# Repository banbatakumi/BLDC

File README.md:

# BLDC

自律走行ミニカー用の BLDC モータドライバ (MD)。**現行のファームは [ProgramV4](ProgramV4/)** (STM32F303K8、FOC、基板 CurcuitV4)。
ProgramV1〜V3 は旧版。

ProgramV4 の文書 (パラメータの意味と根拠の正は `ProgramV4/src/app/config.h`):

| 文書 | 内容 |
|---|---|
| [docs/FOC.md](ProgramV4/docs/FOC.md) | 制御の構成・エンコーダの扱い・スイッチ校正・ゲイン・保護 |
| [docs/SERIAL_PROTOCOL.md](ProgramV4/docs/SERIAL_PROTOCOL.md) | 上位 (STM32F446RE) との UART 通信仕様 |
| [docs/HARDWARE_MAP.md](ProgramV4/docs/HARDWARE_MAP.md) | 基板のピン・相・電流センスの対応 |
| [docs/OPTIMIZATION.md](ProgramV4/docs/OPTIMIZATION.md) | 性能の設計理由・実行時間・残課題 |

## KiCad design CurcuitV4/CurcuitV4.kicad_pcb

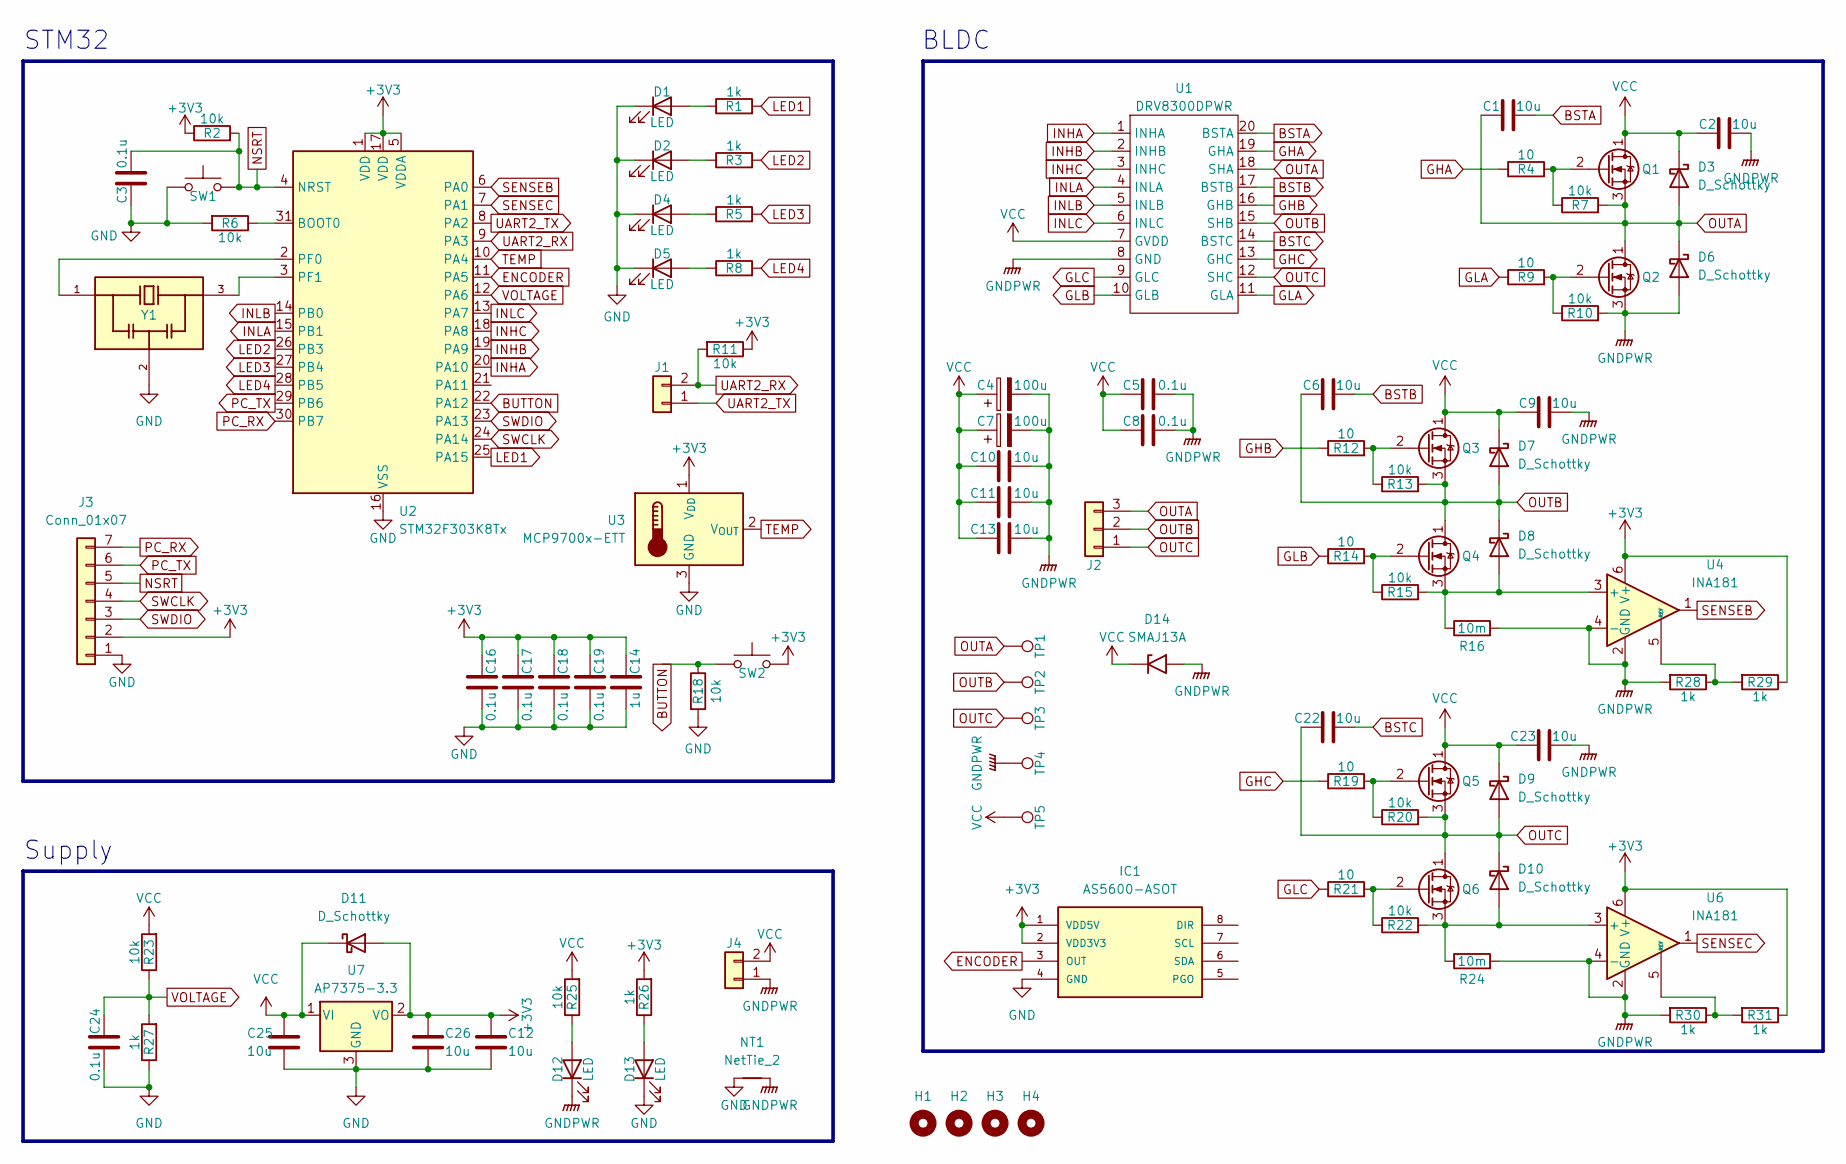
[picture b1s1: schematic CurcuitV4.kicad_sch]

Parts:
C1, C2, C6, C9, C10, C11, C12, C13, C22, C23, C25, C26: 10u; C_0805_2012Metric
C3, C5, C8, C16, C17, C18, C19, C24: 0.1u; C_0603_1608Metric
C4, C7: 100u; CP_Radial_D6.3mm_P2.50mm
C14: 1u; C_0603_1608Metric
D1, D2, D4, D5, D12, D13: LED; LED_0603_1608Metric
D3, D6, D7, D8, D9, D10, D11: D_Schottky; D_SOD-323_HandSoldering
D14: SMAJ13A; D_SMA
H1, H2, H3, H4: MountingHole; MountingHole_3.2mm_M3_ISO14580_Pad_TopBottom
IC1: AS5600-ASOT; SOIC-8_3.9x4.9mm_P1.27mm; MOUSER_PART_NUMBER 985-AS5600-ASOT
J1: Conn_01x02; JST_PH_S2B-PH-K_1x02_P2.00mm_Horizontal
J2: Conn_01x03; Molex_SPOX_5268-03A_1x03_P2.50mm_Horizontal
J3: Conn_01x07; PinSocket_1x07_P2.54mm_Vertical
J4: Conn_01x02; Molex_SPOX_5268-02A_1x02_P2.50mm_Horizontal
NT1: NetTie_2; NetTie-2_SMD_Pad0.5mm
Q1, Q2, Q3, Q4, Q5, Q6: Q_NMOS_DGS; SSM6K819R
R1, R3, R5, R8, R26, R27, R28, R29, R30, R31: 1k; R_0603_1608Metric
R2, R6, R7, R10, R11, R13, R15, R18, R20, R22, R23, R25: 10k; R_0603_1608Metric
R4, R9, R12, R14, R19, R21: 10; R_0603_1608Metric
R16, R24: 10m; R_1206_3216Metric
SW1, SW2: SW_Push; SW_Push_1P1T_NO_Vertical_Wuerth_434133025816
TP1, TP2, TP3, TP4, TP5: TestPoint; TestPoint_Pad_D2.5mm
U1: DRV8300DPWR; TSSOP-20_4.4x6.5mm_P0.65mm
U2: STM32F303K8Tx; LQFP-32_7x7mm_P0.8mm
U3: MCP9700x-ETT; SOT-23
U4, U6: INA181; SOT-23-6
U7: AP7375-3.3; SOT-23
Y1: CSTNE16M0V530000R0; Resonator_SMD_Murata_CSTxExxV-3Pin_3.0x1.1mm; PARTREV JGC42-8853B

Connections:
+3V3: C12.1, C14.2, C16.2, C17.2, C18.2, C19.2, C26.1, D11.2 (A), IC1.1 (VDD5V), IC1.2 (VDD3V3), J3.2, R2.1, R11.1, R26.2, R29.1, R31.1, SW2.2, U2.1 (VDD), U2.5 (VDDA), U2.17 (VDD), U3.1 (V_{DD}), U4.6 (V+), U6.6 (V+), U7.2 (VO)
BSTA: C1.2, U1.20 (BSTA)
BSTB: C6.2, U1.17 (BSTB)
BSTC: C22.2, U1.14 (BSTC)
BUTTON: R18.1, SW2.1, U2.22 (PA12)
ENCODER: IC1.3 (OUT), U2.11 (PA5)
GHA: R4.1, U1.19 (GHA)
GHB: R12.1, U1.16 (GHB)
GHC: R19.1, U1.13 (GHC)
GLA: R9.1, U1.11 (GLA)
GLB: R14.1, U1.10 (GLB)
GLC: R21.1, U1.9 (GLC)
GND: C3.2, C12.2, C14.1, C16.1, C17.1, C18.1, C19.1, C24.1, C25.2, C26.2, D1.1 (K), D2.1 (K), D4.1 (K), D5.1 (K), D13.1 (K), IC1.4 (GND), J3.1, NT1.1, R6.2, R18.2, R27.1, SW1.1, U2.16 (VSS), U2.32 (VSS), U3.3 (GND), U7.3 (GND), Y1.2
GNDPWR: C2.2, C4.2, C5.1, C7.2, C8.1, C9.2, C10.1, C11.1, C13.1, C23.2, D6.2 (A), D12.1 (K), D14.2 (A2), J4.1, NT1.2, Q2.3 (S), R10.2, R16.2, R24.2, R28.2, R30.2, TP4.1, U1.8 (GND), U4.2 (GND), U4.4 (-), U6.2 (GND), U6.4 (-)
INHA: U1.1 (INHA), U2.20 (PA10)
INHB: U1.2 (INHB), U2.19 (PA9)
INHC: U1.3 (INHC), U2.18 (PA8)
INLA: U1.4 (INLA), U2.15 (PB1)
INLB: U1.5 (INLB), U2.14 (PB0)
INLC: U1.6 (INLC), U2.13 (PA7)
LED1: R1.2, U2.25 (PA15)
LED2: R3.2, U2.26 (PB3)
LED3: R5.2, U2.27 (PB4)
LED4: R8.2, U2.28 (PB5)
NSRT: C3.1, J3.5, R2.2, SW1.2, U2.4 (NRST)
unnamed: D1.2 (A), R1.1
unnamed: D2.2 (A), R3.1
unnamed: D4.2 (A), R5.1
unnamed: D5.2 (A), R8.1
unnamed: D8.2 (A), Q4.3 (S), R15.2, R16.1, U4.3 (+)
unnamed: D10.2 (A), Q6.3 (S), R22.2, R24.1, U6.3 (+)
unnamed: D12.2 (A), R25.1
unnamed: D13.2 (A), R26.1
unnamed: Q1.2 (G), R4.2, R7.1
unnamed: Q2.2 (G), R9.2, R10.1
unnamed: Q3.2 (G), R12.2, R13.1
unnamed: Q4.2 (G), R14.2, R15.1
unnamed: Q5.2 (G), R19.2, R20.1
unnamed: Q6.2 (G), R21.2, R22.1
unnamed: R6.1, U2.31 (BOOT0)
unnamed: U2.2 (PF0), Y1.1
unnamed: U2.3 (PF1), Y1.3
unnamed: R28.1, R29.2, U4.5 (REF)
unnamed: R30.1, R31.2, U6.5 (REF)
OUTA: C1.1, D3.2 (A), D6.1 (K), J2.3, Q1.3 (S), Q2.1 (D), R7.2, TP1.1, U1.18 (SHA)
OUTB: C6.1, D7.2 (A), D8.1 (K), J2.2, Q3.3 (S), Q4.1 (D), R13.2, TP2.1, U1.15 (SHB)
OUTC: C22.1, D9.2 (A), D10.1 (K), J2.1, Q5.3 (S), Q6.1 (D), R20.2, TP3.1, U1.12 (SHC)
PC_RX: J3.7, U2.30 (PB7)
PC_TX: J3.6, U2.29 (PB6)
SENSEB: U2.6 (PA0), U4.1
SENSEC: U2.7 (PA1), U6.1
SWCLK: J3.4, U2.24 (PA14)
SWDIO: J3.3, U2.23 (PA13)
TEMP: U2.10 (PA4), U3.2 (V_{OUT})
UART2_RX: J1.2, R11.2, U2.9 (PA3)
UART2_TX: J1.1, U2.8 (PA2)
VCC: C2.1, C4.1, C5.2, C7.1, C8.2, C9.1, C10.2, C11.2, C13.2, C23.1, C25.1, D3.1 (K), D7.1 (K), D9.1 (K), D11.1 (K), D14.1 (A1), J4.2, Q1.1 (D), Q3.1 (D), Q5.1 (D), R23.2, R25.2, TP5.1, U1.7 (GVDD), U7.1 (VI)
VOLTAGE: C24.2, R23.1, R27.2, U2.12 (PA6)

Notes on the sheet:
Supply
STM32
BLDC

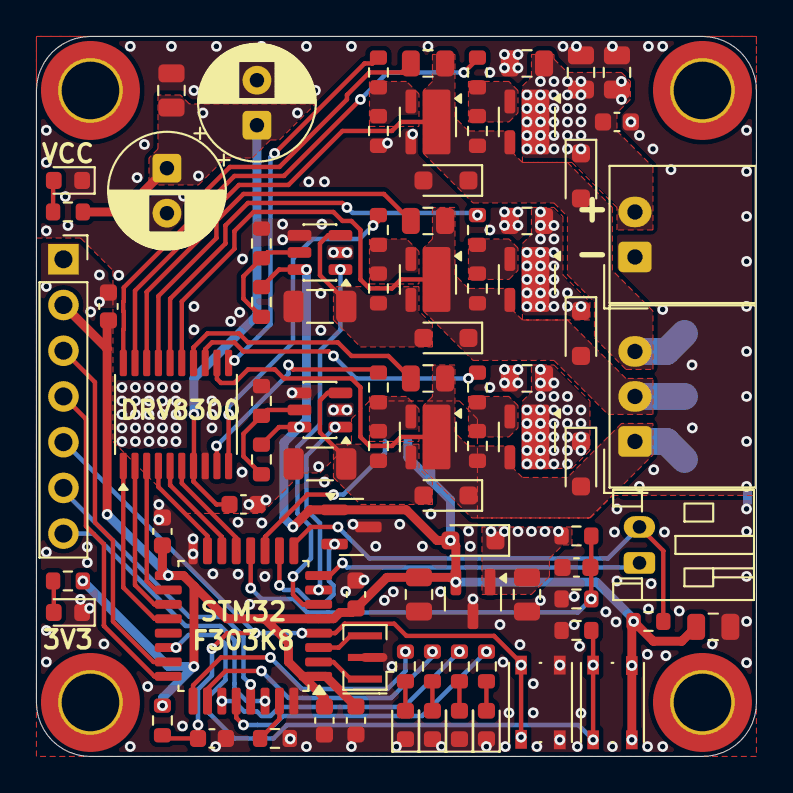
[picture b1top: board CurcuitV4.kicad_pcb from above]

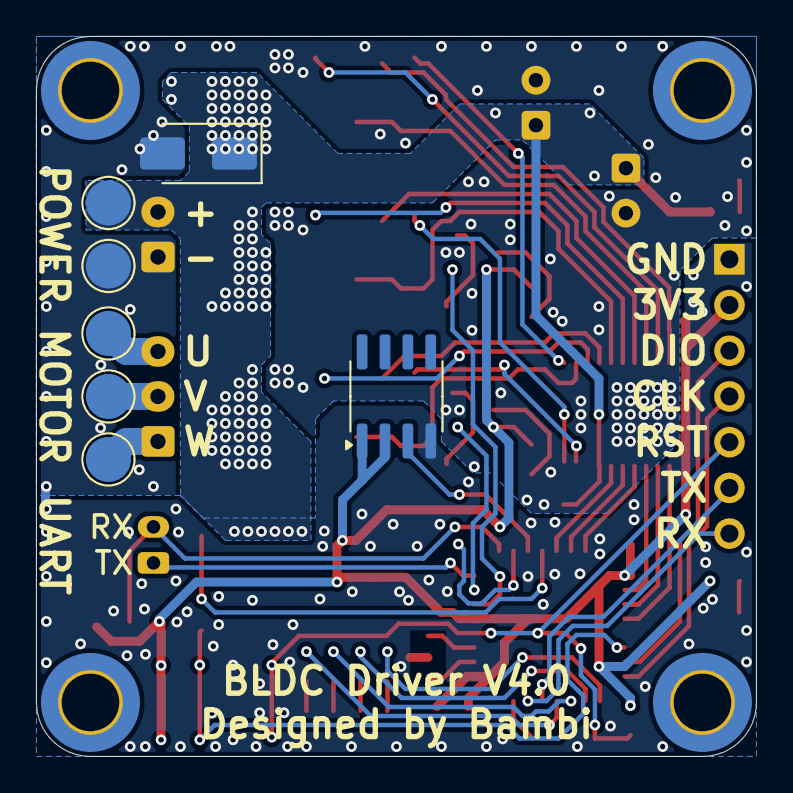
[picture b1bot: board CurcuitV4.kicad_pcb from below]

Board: 2 copper layers, 40.0 x 40.0 mm, 97 parts (8 on the bottom side), 58 nets.

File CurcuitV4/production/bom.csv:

Designator,Footprint,Quantity,Value,LCSC Part #
"C1, C10, C11, C12, C13, C2, C22, C23, C25, C26, C6, C9",0805,12,10u,
C14,0603,1,1u,
"C16, C17, C18, C19, C24, C3, C5, C8",0603,8,0.1u,
"C4, C7",CP_Radial_D6.3mm_P2.50mm,2,100u,
"D1, D12, D13, D2, D4, D5",0603,6,LED,
"D10, D11, D3, D6, D7, D8, D9",D_SOD-323_HandSoldering,7,D_Schottky,
D14,D_SMA,1,SMAJ13A,
IC1,SOIC-8_3.9x4.9mm_P1.27mm,1,AS5600-ASOT,
J1,JST_PH_S2B-PH-K_1x02_P2.00mm_Horizontal,1,Conn_01x02,
J2,Molex_SPOX_5268-03A_1x03_P2.50mm_Horizontal,1,Conn_01x03,
J3,PinSocket_1x07_P2.54mm_Vertical,1,Conn_01x07,
J4,Molex_SPOX_5268-02A_1x02_P2.50mm_Horizontal,1,Conn_01x02,
"Q1, Q2, Q3, Q4, Q5, Q6",SSM6K819R,6,Q_NMOS_DGS,
"R1, R26, R27, R28, R29, R3, R30, R31, R5, R8",0603,10,1k,
"R10, R11, R13, R15, R18, R2, R20, R22, R23, R25, R6, R7",0603,12,10k,
"R12, R14, R19, R21, R4, R9",0603,6,10,
"R16, R24",1206,2,10m,
"SW1, SW2",SW_Push_1P1T_NO_Vertical_Wuerth_434133025816,2,SW_Push,
"TP1, TP2, TP3, TP4, TP5",TestPoint_Pad_D2.5mm,5,TestPoint,
U1,TSSOP-20_4.4x6.5mm_P0.65mm,1,DRV8300DPWR,
U2,LQFP-32_7x7mm_P0.8mm,1,STM32F303K8Tx,
U3,SOT-23,1,MCP9700x-ETT,
"U4, U6",SOT-23-6,2,INA181,
U7,SOT-23,1,AP7375-3.3,
Y1,Resonator_SMD_Murata_CSTxExxV-3Pin_3.0x1.1mm,1,CSTNE16M0V530000R0,

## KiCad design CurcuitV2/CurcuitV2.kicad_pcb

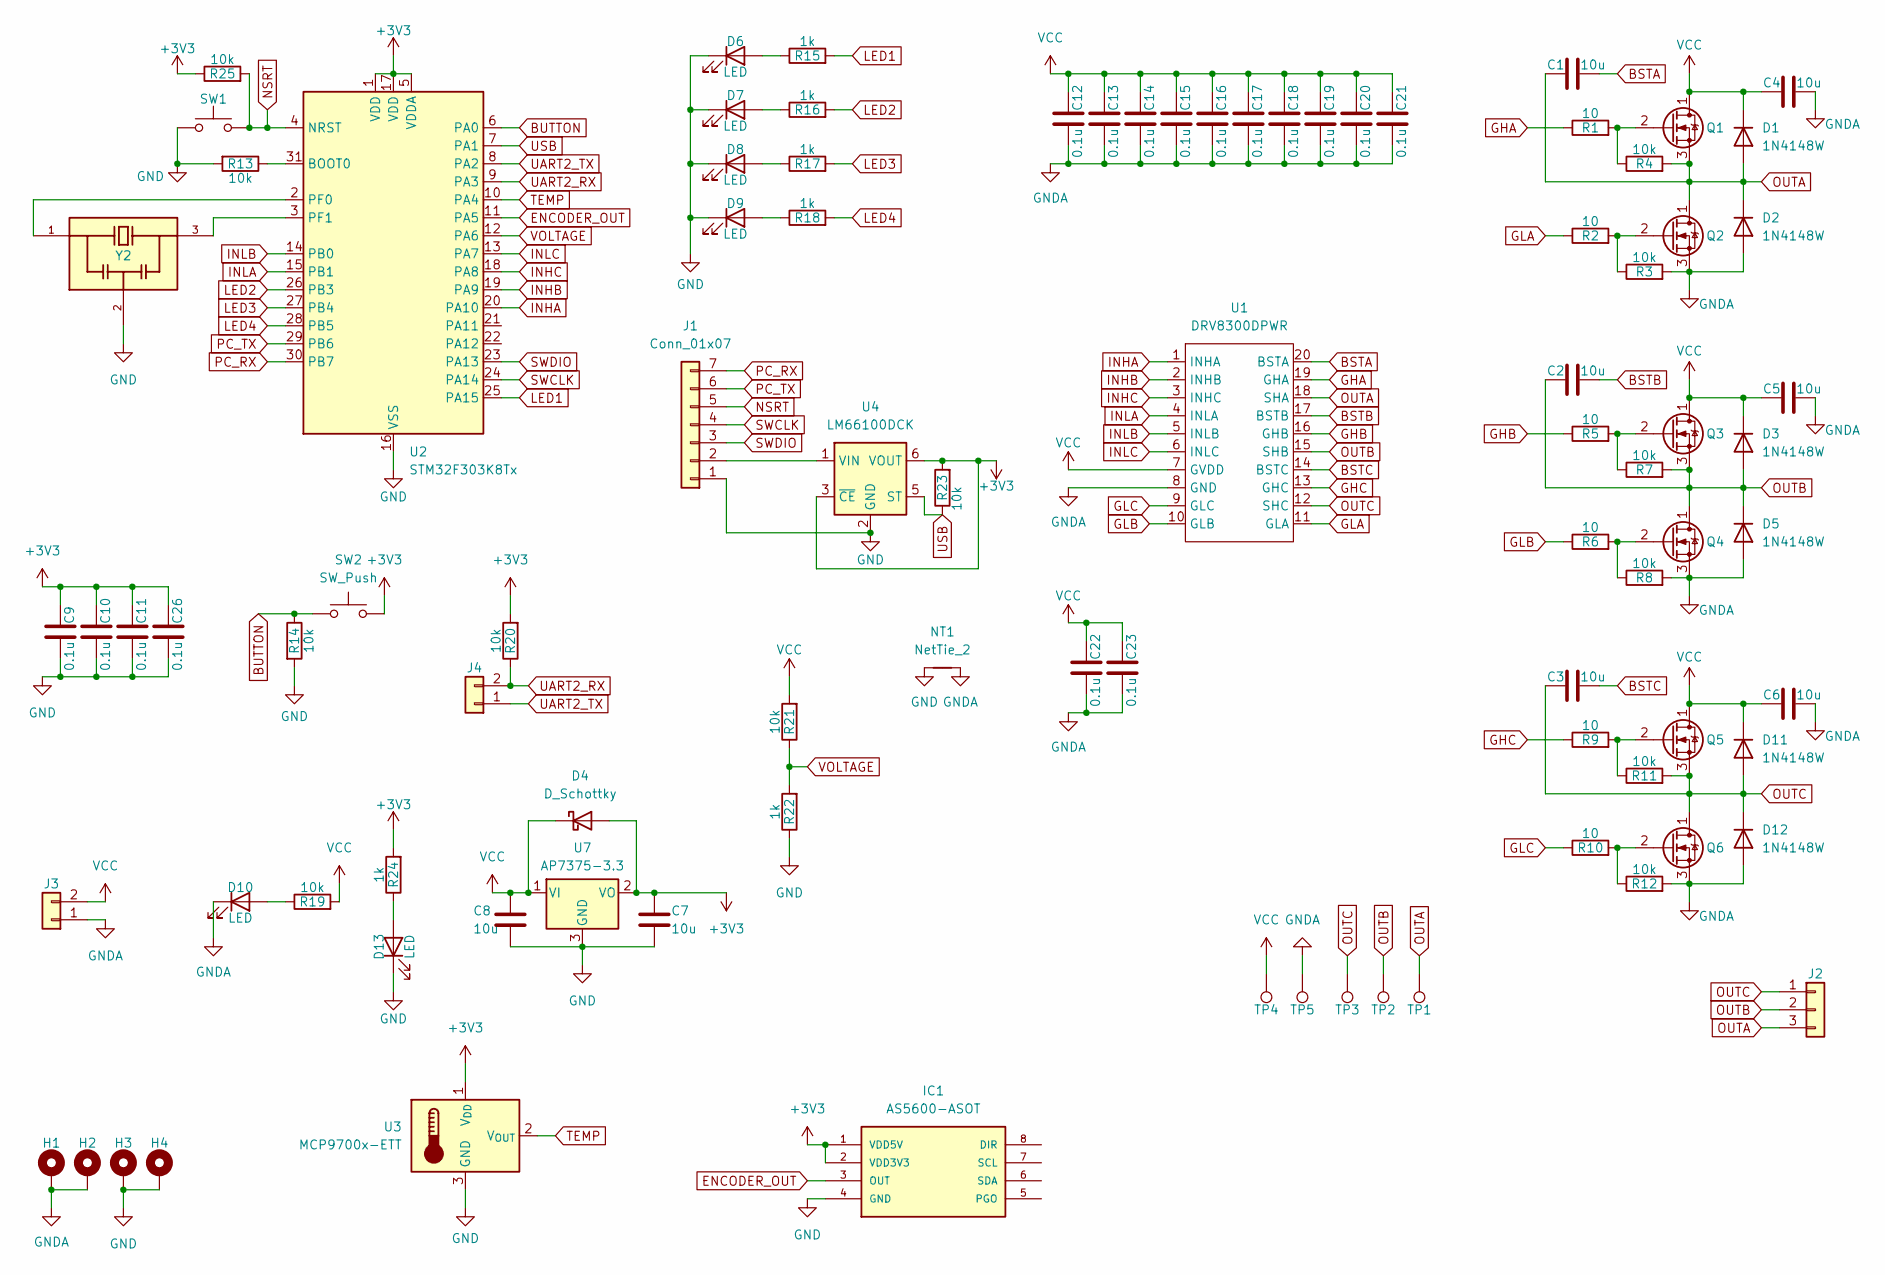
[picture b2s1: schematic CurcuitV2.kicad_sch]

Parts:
C1, C2, C3, C4, C5, C6, C7, C8: 10u; C_0805_2012Metric
C9, C10, C11, C22, C26: 0.1u; C_0603_1608Metric
C12, C13, C14, C15, C16, C17, C18, C19, C20, C21, C23: 0.1u; C_0805_2012Metric
D1, D2, D3, D5, D11, D12: 1N4148W; D_SOD-123
D4: D_Schottky; D_SOD-323_HandSoldering
D6, D7, D8, D9, D10, D13: LED; LED_0603_1608Metric
H1, H2, H3, H4: MountingHole_Pad; MountingHole_3.2mm_M3_ISO14580_Pad_TopBottom
IC1: AS5600-ASOT; SOIC-8_3.9x4.9mm_P1.27mm; MOUSER_PART_NUMBER 985-AS5600-ASOT
J1: Conn_01x07; PinSocket_1x07_P2.54mm_Vertical
J2: Conn_01x03; JST_XH_S3B-XH-A_1x03_P2.50mm_Horizontal
J3: Conn_01x02; JST_XH_S2B-XH-A_1x02_P2.50mm_Horizontal
J4: Conn_01x02; JST_PH_S2B-PH-K_1x02_P2.00mm_Horizontal
NT1: NetTie_2; NetTie-2_SMD_Pad2.0mm
Q1, Q2, Q3, Q4, Q5, Q6: Q_NMOS_DGS; SSM6K819R
R1, R2, R5, R6, R9, R10: 10; R_0603_1608Metric
R3, R4, R7, R8, R11, R12, R13, R14, R19, R20, R21, R23, R25: 10k; R_0603_1608Metric
R15, R16, R17, R18, R22, R24: 1k; R_0603_1608Metric
SW1, SW2: SW_Push; SW_Push_1P1T_NO_Vertical_Wuerth_434133025816
TP1, TP2, TP3, TP4, TP5: TestPoint; TestPoint_Pad_D2.5mm
U1: DRV8300DPWR; TSSOP-20_4.4x6.5mm_P0.65mm
U2: STM32F303K8Tx; LQFP-32_7x7mm_P0.8mm
U3: MCP9700x-ETT; SOT-23
U4: LM66100DCK; SOT-363_SC-70-6
U7: AP7375-3.3; SOT-23
Y2: CSTNE16M0V530000R0; Resonator_SMD_Murata_CSTxExxV-3Pin_3.0x1.1mm; PARTREV JGC42-8853B

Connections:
+3V3: C7.1, C9.2, C10.2, C11.2, C26.2, D4.2 (A), IC1.1 (VDD5V), IC1.2 (VDD3V3), R20.2, R23.2, R24.2, R25.1, SW2.2, U2.1 (VDD), U2.5 (VDDA), U2.17 (VDD), U3.1 (V_{DD}), U4.3 (~CE), U4.6 (VOUT), U7.2 (VO)
BSTA: C1.2, U1.20 (BSTA)
BSTB: C2.2, U1.17 (BSTB)
BSTC: C3.2, U1.14 (BSTC)
BUTTON: R14.1, SW2.1, U2.6 (PA0)
ENCODER_OUT: IC1.3 (OUT), U2.11 (PA5)
GHA: R1.1, U1.19 (GHA)
GHB: R5.1, U1.16 (GHB)
GHC: R9.1, U1.13 (GHC)
GLA: R2.1, U1.11 (GLA)
GLB: R6.1, U1.10 (GLB)
GLC: R10.1, U1.9 (GLC)
GND: C7.2, C8.2, C9.1, C10.1, C11.1, C26.1, D6.1 (K), D7.1 (K), D8.1 (K), D9.1 (K), D13.1 (K), H3.1, H4.1, IC1.4 (GND), J1.1, NT1.1, R13.2, R14.2, R22.1, SW1.1, U2.16 (VSS), U2.32 (VSS), U3.3 (GND), U4.2 (GND), U7.3 (GND), Y2.2; also elsewhere on the board
GNDA: C4.2, C5.2, C6.2, C12.1, C13.1, C14.1, C15.1, C16.1, C17.1, C18.1, C19.1, C20.1, C21.1, C22.1, C23.1, D2.2 (A), D5.2 (A), D10.1 (K), D12.2 (A), H1.1, H2.1, J3.1, NT1.2, Q2.3 (S), Q4.3 (S), Q6.3 (S), R3.2, R8.2, R12.2, TP5.1, U1.8 (GND)
INHA: U1.1 (INHA), U2.20 (PA10)
INHB: U1.2 (INHB), U2.19 (PA9)
INHC: U1.3 (INHC), U2.18 (PA8)
INLA: U1.4 (INLA), U2.15 (PB1)
INLB: U1.5 (INLB), U2.14 (PB0)
INLC: U1.6 (INLC), U2.13 (PA7)
LED1: R15.2, U2.25 (PA15)
LED2: R16.2, U2.26 (PB3)
LED3: R17.2, U2.27 (PB4)
LED4: R18.2, U2.28 (PB5)
NSRT: J1.5, R25.2, SW1.2, U2.4 (NRST); also elsewhere on the board
unnamed: D6.2 (A), R15.1
unnamed: D7.2 (A), R16.1
unnamed: D8.2 (A), R17.1
unnamed: D9.2 (A), R18.1
unnamed: D10.2 (A), R19.1
unnamed: D13.2 (A), R24.1
unnamed: J1.2, U4.1 (VIN)
unnamed: Q1.2 (G), R1.2, R4.1
unnamed: Q2.2 (G), R2.2, R3.1
unnamed: Q3.2 (G), R5.2, R7.1
unnamed: Q4.2 (G), R6.2, R8.1
unnamed: Q5.2 (G), R9.2, R11.1
unnamed: Q6.2 (G), R10.2, R12.1
unnamed: R13.1, U2.31 (BOOT0)
unnamed: U2.2 (PF0), Y2.1
unnamed: U2.3 (PF1), Y2.3
OUTA: C1.1, D1.2 (A), D2.1 (K), J2.3, Q1.3 (S), Q2.1 (D), R4.2, TP1.1, U1.18 (SHA)
OUTB: C2.1, D3.2 (A), D5.1 (K), J2.2, Q3.3 (S), Q4.1 (D), R7.2, TP2.1, U1.15 (SHB)
OUTC: C3.1, D11.2 (A), D12.1 (K), J2.1, Q5.3 (S), Q6.1 (D), R11.2, TP3.1, U1.12 (SHC)
PC_RX: J1.7, U2.30 (PB7)
PC_TX: J1.6, U2.29 (PB6)
SWCLK: J1.4, U2.24 (PA14)
SWDIO: J1.3, U2.23 (PA13)
TEMP: U2.10 (PA4), U3.2 (V_{OUT})
UART2_RX: J4.2, R20.1, U2.9 (PA3)
UART2_TX: J4.1, U2.8 (PA2)
USB: R23.1, U2.7 (PA1), U4.5 (ST)
VCC: C4.1, C5.1, C6.1, C8.1, C12.2, C13.2, C14.2, C15.2, C16.2, C17.2, C18.2, C19.2, C20.2, C21.2, C22.2, C23.2, D1.1 (K), D3.1 (K), D4.1 (K), D11.1 (K), J3.2, Q1.1 (D), Q3.1 (D), Q5.1 (D), R19.2, R21.2, TP4.1, U1.7 (GVDD), U7.1 (VI)
VOLTAGE: R21.1, R22.2, U2.12 (PA6)

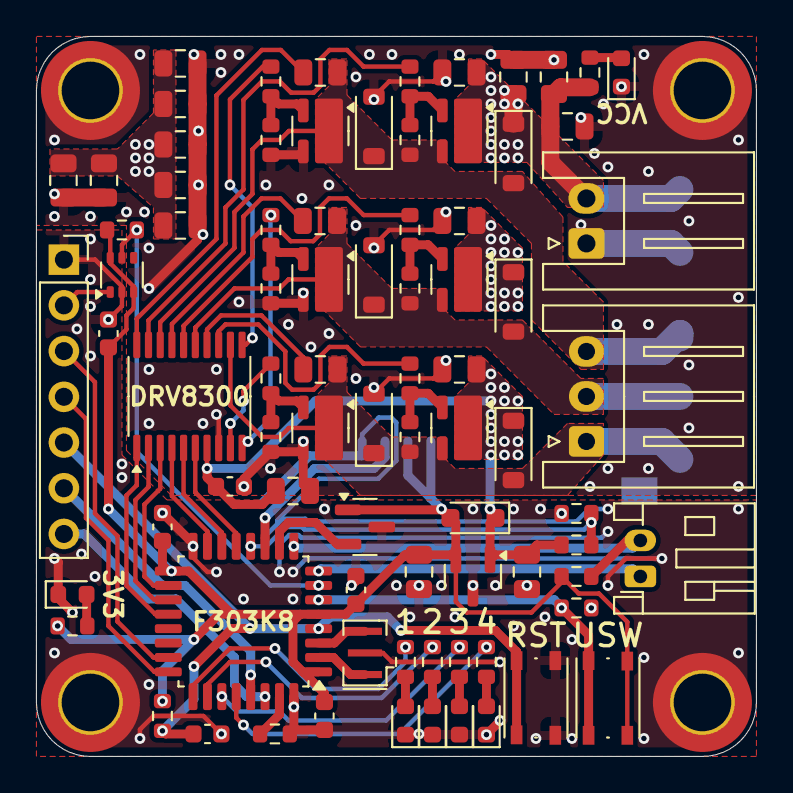
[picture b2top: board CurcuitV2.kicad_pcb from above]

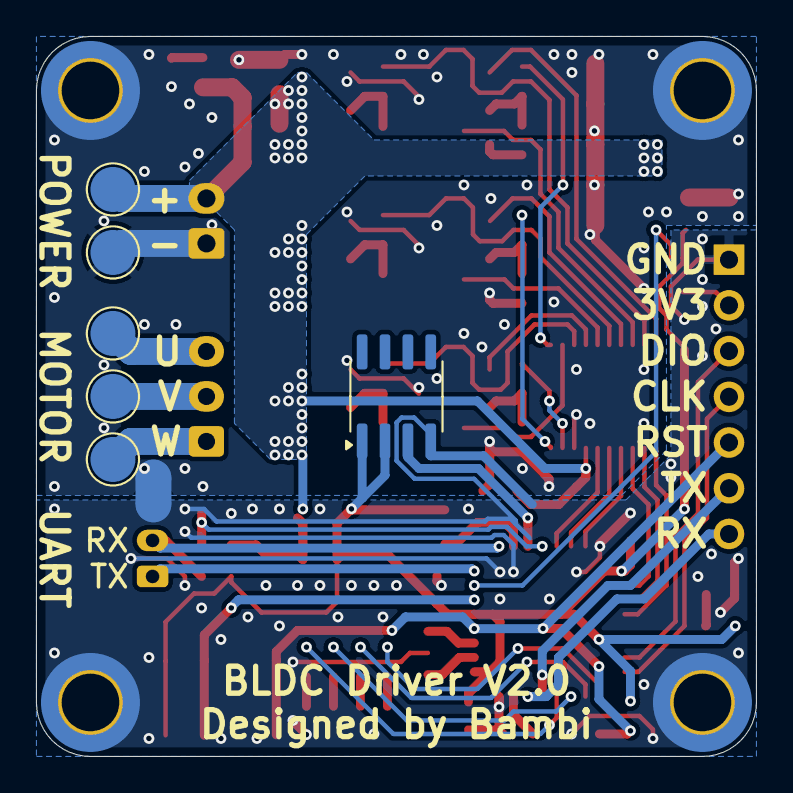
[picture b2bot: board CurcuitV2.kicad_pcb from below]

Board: 2 copper layers, 40.0 x 40.0 mm, 92 parts (7 on the bottom side), 54 nets.

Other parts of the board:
C24: 0.1u; C_0603_1608Metric

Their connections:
GND: C24.2; also elsewhere on the board
NSRT: C24.1; also elsewhere on the board

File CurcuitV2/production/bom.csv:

Designator,Footprint,Quantity,Value,LCSC Part #
"C1, C2, C3, C4, C5, C6, C7, C8",0805,8,10u,
"C10, C11, C22, C26, C9",0603,5,0.1u,
"C12, C13, C14, C15, C16, C17, C18, C19, C20, C21, C23",0805,11,0.1u,
"D1, D11, D12, D2, D3, D5",D_SOD-123,6,1N4148W,
"D10, D13, D6, D7, D8, D9",0603,6,LED,
D4,D_SOD-323_HandSoldering,1,D_Schottky,
IC1,SOIC-8_3.9x4.9mm_P1.27mm,1,AS5600-ASOT,
J1,PinSocket_1x07_P2.54mm_Vertical,1,Conn_01x07,
J2,JST_XH_S3B-XH-A_1x03_P2.50mm_Horizontal,1,Conn_01x03,
J3,JST_XH_S2B-XH-A_1x02_P2.50mm_Horizontal,1,Conn_01x02,
J4,JST_PH_S2B-PH-K_1x02_P2.00mm_Horizontal,1,Conn_01x02,
"Q1, Q2, Q3, Q4, Q5, Q6",SSM6K819R,6,Q_NMOS_DGS,
"R1, R10, R2, R5, R6, R9",0603,6,10,
"R11, R12, R13, R14, R19, R20, R21, R23, R3, R4, R7, R8",0603,12,10k,
"R15, R16, R17, R18, R22, R24",0603,6,1k,
"SW1, SW2",SW_Push_1P1T_NO_Vertical_Wuerth_434133025816,2,SW_Push,
"TP1, TP2, TP3, TP4, TP5",TestPoint_Pad_D2.5mm,5,TestPoint,
U1,TSSOP-20_4.4x6.5mm_P0.65mm,1,DRV8300DPWR,
U2,LQFP-32_7x7mm_P0.8mm,1,STM32F303K8Tx,
U3,SOT-23,1,MCP9700x-ETT,
U4,SOT-363_SC-70-6,1,LM66100DCK,
U7,SOT-23,1,AP7375-3.3,
Y2,Resonator_SMD_Murata_CSTxExxV-3Pin_3.0x1.1mm,1,CSTNE16M0V530000R0,

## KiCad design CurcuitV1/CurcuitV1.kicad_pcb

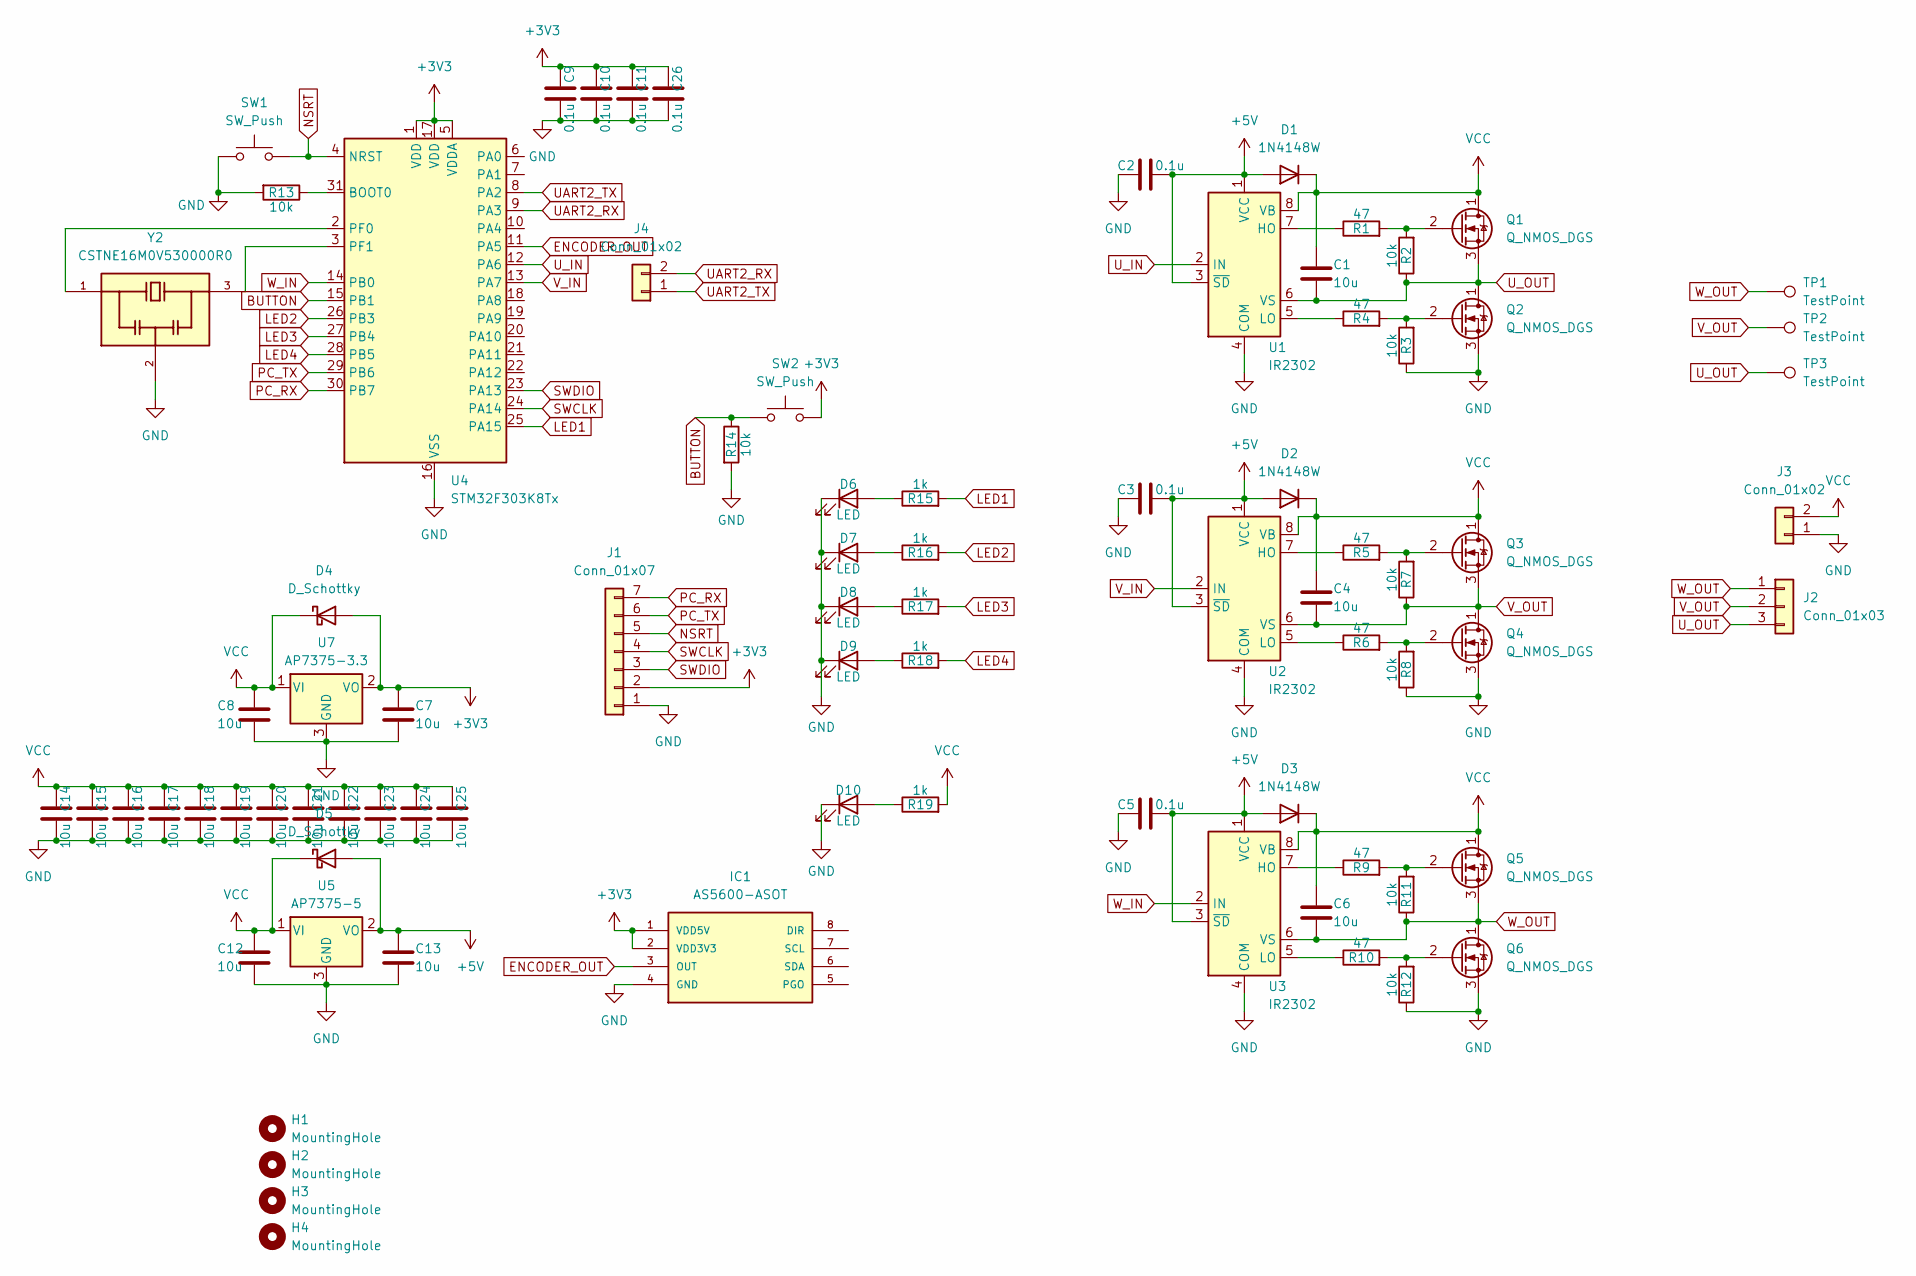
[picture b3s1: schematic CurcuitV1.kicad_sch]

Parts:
C1, C4, C6, C7, C8, C12, C13, C14, C15, C16, C17, C18, C19, C20, C21, C22, C23, C24, C25: 10u; C_0805_2012Metric
C2, C3, C5, C9, C10, C11, C26: 0.1u; C_0603_1608Metric
D1, D2, D3: 1N4148W; D_SOD-123
D4, D5: D_Schottky; D_SOD-323_HandSoldering
D6, D7, D8, D9, D10: LED; LED_0603_1608Metric
H1, H2, H3, H4: MountingHole; MountingHole_3.2mm_M3_DIN965_Pad
IC1: AS5600-ASOT; SOIC-8_3.9x4.9mm_P1.27mm; MOUSER_PART_NUMBER 985-AS5600-ASOT
J1: Conn_01x07; PinSocket_1x07_P2.54mm_Vertical
J2: Conn_01x03; JST_XH_S3B-XH-A_1x03_P2.50mm_Horizontal
J3, J4: Conn_01x02; JST_XH_S2B-XH-A_1x02_P2.50mm_Horizontal
Q1, Q2, Q3, Q4, Q5, Q6: Q_NMOS_DGS; SSM6K819R
R1, R4, R5, R6, R9, R10: 47; R_0603_1608Metric
R2, R3, R7, R8, R11, R12, R13, R14: 10k; R_0603_1608Metric
R15, R16, R17, R18, R19: 1k; R_0603_1608Metric
SW1, SW2: SW_Push; SW_Push_1P1T_NO_Vertical_Wuerth_434133025816
TP1, TP2, TP3: TestPoint; TestPoint_Pad_D2.0mm
U1, U2, U3: IR2302; SOP-8_3.9x4.9mm_P1.27mm
U4: STM32F303K8Tx; LQFP-32_7x7mm_P0.8mm
U5: AP7375-5; SOT-23
U7: AP7375-3.3; SOT-23
Y2: CSTNE16M0V530000R0; OSC_CSTNE16M0V530000R0; PARTREV JGC42-8853B

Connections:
+3V3: C7.1, C9.2, C10.2, C11.2, C26.2, D4.2 (A), IC1.1 (VDD5V), IC1.2 (VDD3V3), J1.2, SW2.2, U4.1 (VDD), U4.5 (VDDA), U4.17 (VDD), U7.2 (VO)
+5V: C2.1, C3.1, C5.1, C13.1, D1.2 (A), D2.2 (A), D3.2 (A), D5.2 (A), U1.1 (VCC), U1.3 (~SD), U2.1 (VCC), U2.3 (~SD), U3.1 (VCC), U3.3 (~SD), U5.2 (VO)
BUTTON: R14.1, SW2.1, U4.15 (PB1)
ENCODER_OUT: IC1.3 (OUT), U4.11 (PA5)
GND: C2.2, C3.2, C5.2, C7.2, C8.2, C9.1, C10.1, C11.1, C12.2, C13.2, C14.1, C15.1, C16.1, C17.1, C18.1, C19.1, C20.1, C21.1, C22.1, C23.1, C24.1, C25.1, C26.1, D6.1 (K), D7.1 (K), D8.1 (K), D9.1 (K), D10.1 (K), IC1.4 (GND), J1.1, J3.1, Q2.3 (S), Q4.3 (S), Q6.3 (S), R3.1, R8.1, R12.1, R13.2, R14.2, SW1.1, U1.4 (COM), U2.4 (COM), U3.4 (COM), U4.16 (VSS), U4.32 (VSS), U5.3 (GND), U7.3 (GND), Y2.2
LED1: R15.2, U4.25 (PA15)
LED2: R16.2, U4.26 (PB3)
LED3: R17.2, U4.27 (PB4)
LED4: R18.2, U4.28 (PB5)
NSRT: J1.5, SW1.2, U4.4 (NRST)
unnamed: D6.2 (A), R15.1
unnamed: D7.2 (A), R16.1
unnamed: D8.2 (A), R17.1
unnamed: D9.2 (A), R18.1
unnamed: D10.2 (A), R19.1
unnamed: Q1.2 (G), R1.2, R2.2
unnamed: Q2.2 (G), R3.2, R4.2
unnamed: Q3.2 (G), R5.2, R7.2
unnamed: Q4.2 (G), R6.2, R8.2
unnamed: Q5.2 (G), R9.2, R11.2
unnamed: Q6.2 (G), R10.2, R12.2
unnamed: R1.1, U1.7 (HO)
unnamed: R4.1, U1.5 (LO)
unnamed: R5.1, U2.7 (HO)
unnamed: R6.1, U2.5 (LO)
unnamed: R9.1, U3.7 (HO)
unnamed: R10.1, U3.5 (LO)
unnamed: R13.1, U4.31 (BOOT0)
unnamed: U4.2 (PF0), Y2.1
unnamed: U4.3 (PF1), Y2.3
PC_RX: J1.7, U4.30 (PB7)
PC_TX: J1.6, U4.29 (PB6)
SWCLK: J1.4, U4.24 (PA14)
SWDIO: J1.3, U4.23 (PA13)
UART2_RX: J4.2, U4.9 (PA3)
UART2_TX: J4.1, U4.8 (PA2)
U_IN: U1.2 (IN), U4.12 (PA6)
U_OUT: C1.2, J2.3, Q1.3 (S), Q2.1 (D), R2.1, TP3.1, U1.6 (VS)
VCC: C1.1, C4.1, C6.1, C8.1, C12.1, C14.2, C15.2, C16.2, C17.2, C18.2, C19.2, C20.2, C21.2, C22.2, C23.2, C24.2, C25.2, D1.1 (K), D2.1 (K), D3.1 (K), D4.1 (K), D5.1 (K), J3.2, Q1.1 (D), Q3.1 (D), Q5.1 (D), R19.2, U1.8 (VB), U2.8 (VB), U3.8 (VB), U5.1 (VI), U7.1 (VI)
V_IN: U2.2 (IN), U4.13 (PA7)
V_OUT: C4.2, J2.2, Q3.3 (S), Q4.1 (D), R7.1, TP2.1, U2.6 (VS)
W_IN: U3.2 (IN), U4.14 (PB0)
W_OUT: C6.2, J2.1, Q5.3 (S), Q6.1 (D), R11.1, TP1.1, U3.6 (VS)

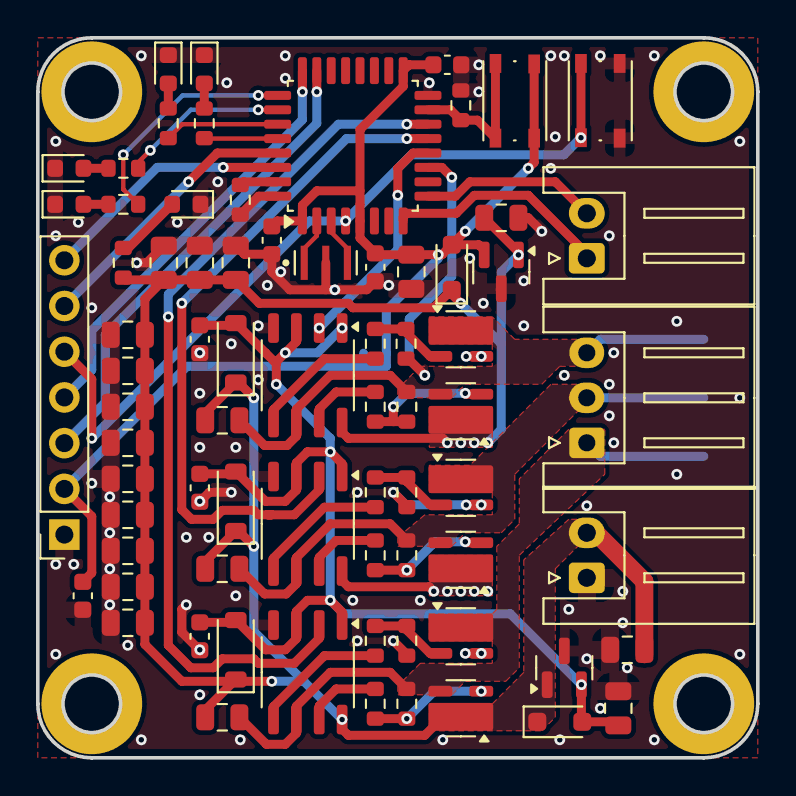
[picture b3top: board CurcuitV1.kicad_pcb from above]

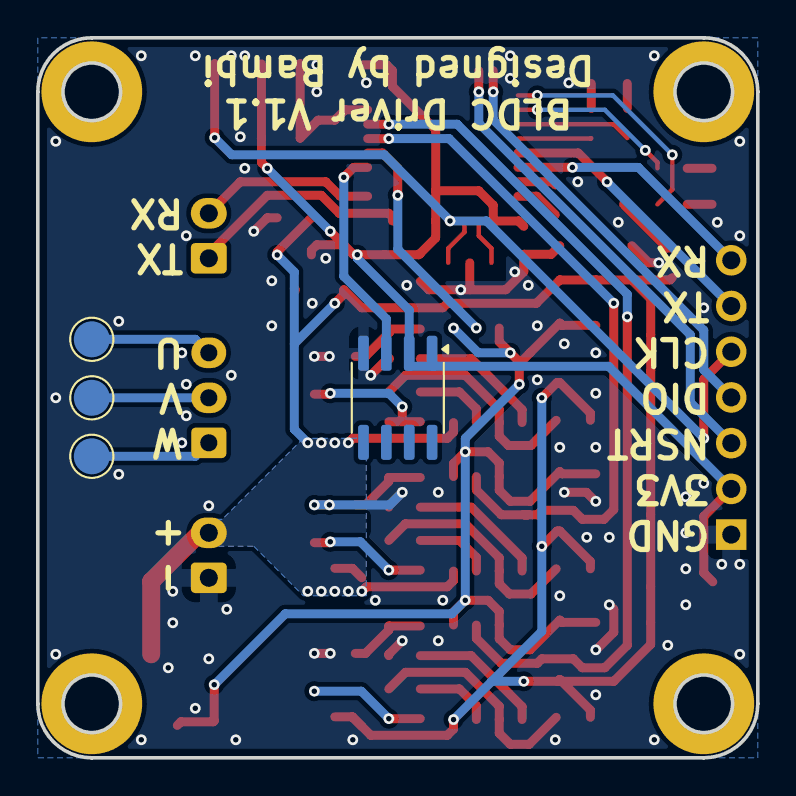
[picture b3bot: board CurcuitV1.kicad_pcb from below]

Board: 2 copper layers, 40.0 x 40.0 mm, 82 parts (4 on the bottom side), 43 nets.

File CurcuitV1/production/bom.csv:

Designator,Footprint,Quantity,Value,LCSC Part #
"C1, C12, C13, C14, C15, C16, C17, C18, C19, C20, C21, C22, C23, C24, C25, C4, C6, C7, C8",0805,19,10u,
"C10, C11, C2, C26, C3, C5, C9",0603,7,0.1u,
"D1, D2, D3",D_SOD-123,3,1N4148W,
"D10, D6, D7, D8, D9",0603,5,LED,
"D4, D5",D_SOD-323_HandSoldering,2,D_Schottky,
IC1,SOIC-8_3.9x4.9mm_P1.27mm,1,AS5600-ASOT,
J1,PinSocket_1x07_P2.54mm_Vertical,1,Conn_01x07,
J2,JST_XH_S3B-XH-A_1x03_P2.50mm_Horizontal,1,Conn_01x03,
"J3, J4",JST_XH_S2B-XH-A_1x02_P2.50mm_Horizontal,2,Conn_01x02,
"Q1, Q2, Q3, Q4, Q5, Q6",SSM6K819R,6,Q_NMOS_DGS,
"R1, R10, R4, R5, R6, R9",0603,6,47,
"R11, R12, R13, R14, R2, R3, R7, R8",0603,8,10k,
"R15, R16, R17, R18, R19",0603,5,1k,
"SW1, SW2",SW_Push_1P1T_NO_Vertical_Wuerth_434133025816,2,SW_Push,
"TP1, TP2, TP3",TestPoint_Pad_D2.0mm,3,TestPoint,
"U1, U2, U3",SOP-8_3.9x4.9mm_P1.27mm,3,IR2302,
U4,LQFP-32_7x7mm_P0.8mm,1,STM32F303K8Tx,
U5,SOT-23,1,AP7375-5,
U7,SOT-23,1,AP7375-3.3,
Y2,OSC_CSTNE16M0V530000R0,1,CSTNE16M0V530000R0,

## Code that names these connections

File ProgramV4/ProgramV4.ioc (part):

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Mcu.Name=STM32F303K(6-8)Tx
Mcu.Package=LQFP32
Mcu.UserName=STM32F303K8Tx
PA0.Mode=IN1-Single-Ended
PA0.Signal=ADC1_IN1
PA1.Mode=IN2-Single-Ended
PA1.Signal=ADC1_IN2
PA10.Signal=S_TIM1_CH3
PA11.Signal=GPIO_Input
PA12.Signal=GPIO_Input
PA13.Mode=Serial_Wire
PA13.Signal=SYS_JTMS-SWDIO
PA14.Mode=Serial_Wire
PA14.Signal=SYS_JTCK-SWCLK
PA15.GPIOParameters=GPIO_Label
PA15.GPIO_Label=LED1
PA15.Signal=S_TIM2_CH1_ETR
PA2.Mode=Asynchronous
PA2.Signal=USART2_TX
PA3.Mode=Asynchronous
PA3.Signal=USART2_RX
PA4.GPIOParameters=GPIO_Label
PA4.GPIO_Label=TEMP
PA4.Mode=IN1-Single-Ended
PA4.Signal=ADC2_IN1
PA5.GPIOParameters=GPIO_Label
PA5.GPIO_Label=ENCODER
PA5.Mode=IN2-Single-Ended
PA5.Signal=ADC2_IN2
PA6.GPIOParameters=GPIO_Label
PA6.GPIO_Label=VOLTAGE
PA6.Mode=IN3-Single-Ended
PA6.Signal=ADC2_IN3
PA7.Mode=PWM Generation1 CH1 CH1N
PA7.Signal=TIM1_CH1N
PA8.Signal=S_TIM1_CH1
PA9.Signal=S_TIM1_CH2
PB0.Mode=PWM Generation2 CH2 CH2N
PB0.Signal=TIM1_CH2N
PB1.Mode=PWM Generation3 CH3 CH3N
PB1.Signal=TIM1_CH3N
PB3.GPIOParameters=GPIO_Label
PB3.GPIO_Label=LED2
PB3.Signal=S_TIM2_CH2
PB4.GPIOParameters=GPIO_Label
PB4.GPIO_Label=LED3
PB4.Signal=S_TIM3_CH1
PB5.GPIOParameters=GPIO_Label
PB5.GPIO_Label=LED4
PB5.Signal=S_TIM3_CH2
PB6.Mode=Asynchronous
PB6.Signal=USART1_TX
PB7.Mode=Asynchronous
PB7.Signal=USART1_RX
PF0\ /\ OSC_IN.Mode=HSE-External-Oscillator
PF0\ /\ OSC_IN.Signal=RCC_OSC_IN
PF1\ /\ OSC_OUT.Mode=HSE-External-Oscillator
PF1\ /\ OSC_OUT.Signal=RCC_OSC_OUT
RCC.HSEPLLFreq_Value=8000000
RCC.HSE_VALUE=16000000
RCC.SYSCLKFreq_VALUE=72000000
RCC.SYSCLKSourceVirtual=RCC_SYSCLKSOURCE_PLLCLK
board=custom

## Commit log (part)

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2025-06-04 大体の部品追加
2025-06-05 水晶追加など
2025-06-05 一旦ジェネレートしてみた
2025-06-05 基板外径仮案
2025-06-05 ピン設定変更
2025-06-05 大体完成
2025-06-05 ピンほぼ決定
2025-06-05 LED配線
2025-06-05 ADCのピン設定
2025-06-05 発注した
2025-06-07 Fusion用の画像出力
2025-06-09 PWMとADCの設定
2025-06-09 makeできた
2025-06-09 app追加
2025-06-10 gitignoreの追加
2025-06-10 Lチカできた
2025-06-10 Remove build directory from git tracking
2025-06-10 mymathの追加&命名変更
2025-06-10 pwm成功
2025-06-10 タイマー追加
2025-06-10 uvwのpwm出力確認
2025-06-10 オープンループコントロール
2025-06-12 ADCの設定ちょっと変更
2025-06-12 V1.1発注
2025-06-20 製造ファイル
2025-06-20 動作試験
2025-06-24 デバッグ
2025-06-25 debug
2025-06-25 DRV8300のライブラリを追加
2025-06-25 必要な部品の挿入ほぼ完了
2025-06-25 CubeMX生成
2025-06-26 ほぼ完成
2025-06-27 製造ファイル生成
2025-06-27 理想ダイオードの追加
2025-06-28 シルクの追加
2025-06-28 GNDビア修正
2025-06-29 GNDビアの修正
2025-06-30 電源LEDの追加
2025-06-30 ちょっとした修正
2025-06-30 NRSTのプルアップ
2025-06-30 NRSTに0.1uf追加
2025-06-30 リファレンス削除
2025-06-30 配線修正
2025-07-04 最終発注ファイル
2025-07-07 強制転流で回った！
2025-07-08 adc読めた
2025-07-08 gitignore追加
2025-07-08 キャッシュ削除
2025-07-08 エンコーダー使ったBLDCの制御できた！
2025-07-08 速度制御できた！
2025-07-08 ちゃんと使えるくらいの制御できた
2025-07-08 エンコーダー値にlpfかけた
2025-07-08 制御周期変更
2025-07-09 位置制御追加
2025-07-09 正逆で消費電流が異なる問題ちょっと解決
2025-07-10 バグ修正
2025-07-10 なんかおかしいと思ったらエンコーダーのオフセットするの忘れてた！直った！寝る！
2025-07-11 エンコーダー初期化処理の変更
2025-07-11 オフセット値を初期設定するようにした
2025-07-11 コメントアウト追加
2025-07-11 オーバーヒートで機能を停止するようにした
2025-07-11 電源電圧の制限
2025-07-11 lpfフィルタライブラリの追加
2025-07-12 エンコーダー値に可変ゲインLPFをかけて低速時に安定させた
2025-07-12 ポジションコントロールPIDを可変Dゲインにした
2025-07-17 新しいBLDCにパラメーターを調整した
2025-07-19 uart2でシリアル通信できた
2025-07-19 タイマー割り込みで2khz制御実装and UARTのバッファクリア処理など通信関連の改善
2025-07-20 コメントアウトの整理
2025-07-20 atan2近似などにより処理の高速化
2025-07-20 最大加速度を制限かけた
2025-07-20 uartを全部dmaにした
2025-07-20 制御周期早くした
2025-07-21 高速域回るようになった
2025-07-24 進化した（忘れた）
2025-07-24 フラッシュにエンコーダーのオフセットなどを保存できるようにした
2025-07-24 環境構築＆GPTで生成したコード貼り付け
2025-07-24 制御モードの追加
2025-07-24 送信値の修正
2025-07-24 add gitignore
2025-07-24 キャッシュクリア
2025-07-24 gitignore修正
2025-07-26 uartの通信プロトコル仮確定
2025-07-29 高周波化&速度測定周期変更
2026-03-31 割り込みの開始をセットアップ後に変更
2026-05-03 ブレーキ実装
2026-05-07 floatに統一
2026-05-07 データ型をdoubleからfloatに変更し、ローパスフィルタの初期化と更新関数を最適化
2026-05-07 ADCサンプリング時間を19サイクルから7サイクルに変更し、BLDC制御の最適化を実施
2026-05-07 ADCサンプリング時間を19サイクルおよび181サイクルに変更し、設定を最適化。温度制限を70°Cに更新。
2026-05-08 RCC設定を最適化し、タイマーのプリスケーラと周期を調整。BLDC制御のPIDパラメータを更新し、LED制御のロジックを修正。
2026-05-08 タイマー設定を最適化し、BLDC制御の三相正弦波生成をarm_mathライブラリを使用して改善。ADCサンプリング時間を調整し、コードの可読性を向上させるために一貫性を持たせた。
2026-05-08 Refactor main application and remove TIM6 functionality
    - Removed TIM6 initialization and interrupt handling from main.c and stm32f3xx_it.c.
    - Updated the timer initialization for TIM1, TIM2, and TIM3 in tim.c.
    - Refactored the main application logic in app.c to handle serial communication and control modes without relying on TIM6.
    - Introduced a new RecvSerial function to manage incoming serial data and control modes.
    - Updated the SendSerial function to send relevant data at specified intervals.
    - Removed unnecessary variables and simplified the control flow in the MainApp function.
2026-05-12 Refactor BLDC control structure and update variable names for clarity; optimize function signatures and enhance angular speed control logic.
2026-05-12 Update USART baud rates to 250000 for improved communication speed
2026-05-14 Refactor BLDC control logic: rename target_torque to target_voltage, update control functions, and optimize filter coefficients for improved performance.
2026-05-16 Refactor BLDC control functions: simplify BLDC_Stop function, enhance control logic, and update MAX_AMP_VOLT to improve performance.
2026-05-19 Refactor BLDC control logic: update TIM1 period for improved timing accuracy, modify serial data structure to include temperature, and enhance PID control logic with integral enable flag.
2026-05-28 Copy From V2
2026-05-28 電流センス部品の追加
2026-05-29 回路ほぼ完成
2026-05-29 MX生成
2026-05-30 回路完成
2026-05-30 シルク書いた
2026-06-03 製造ファイル再生成
2026-06-05 V3の修正と製造ファイル生成
